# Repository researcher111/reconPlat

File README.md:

reconPlat
=========

Reconfigurable platform for prototyping wearables

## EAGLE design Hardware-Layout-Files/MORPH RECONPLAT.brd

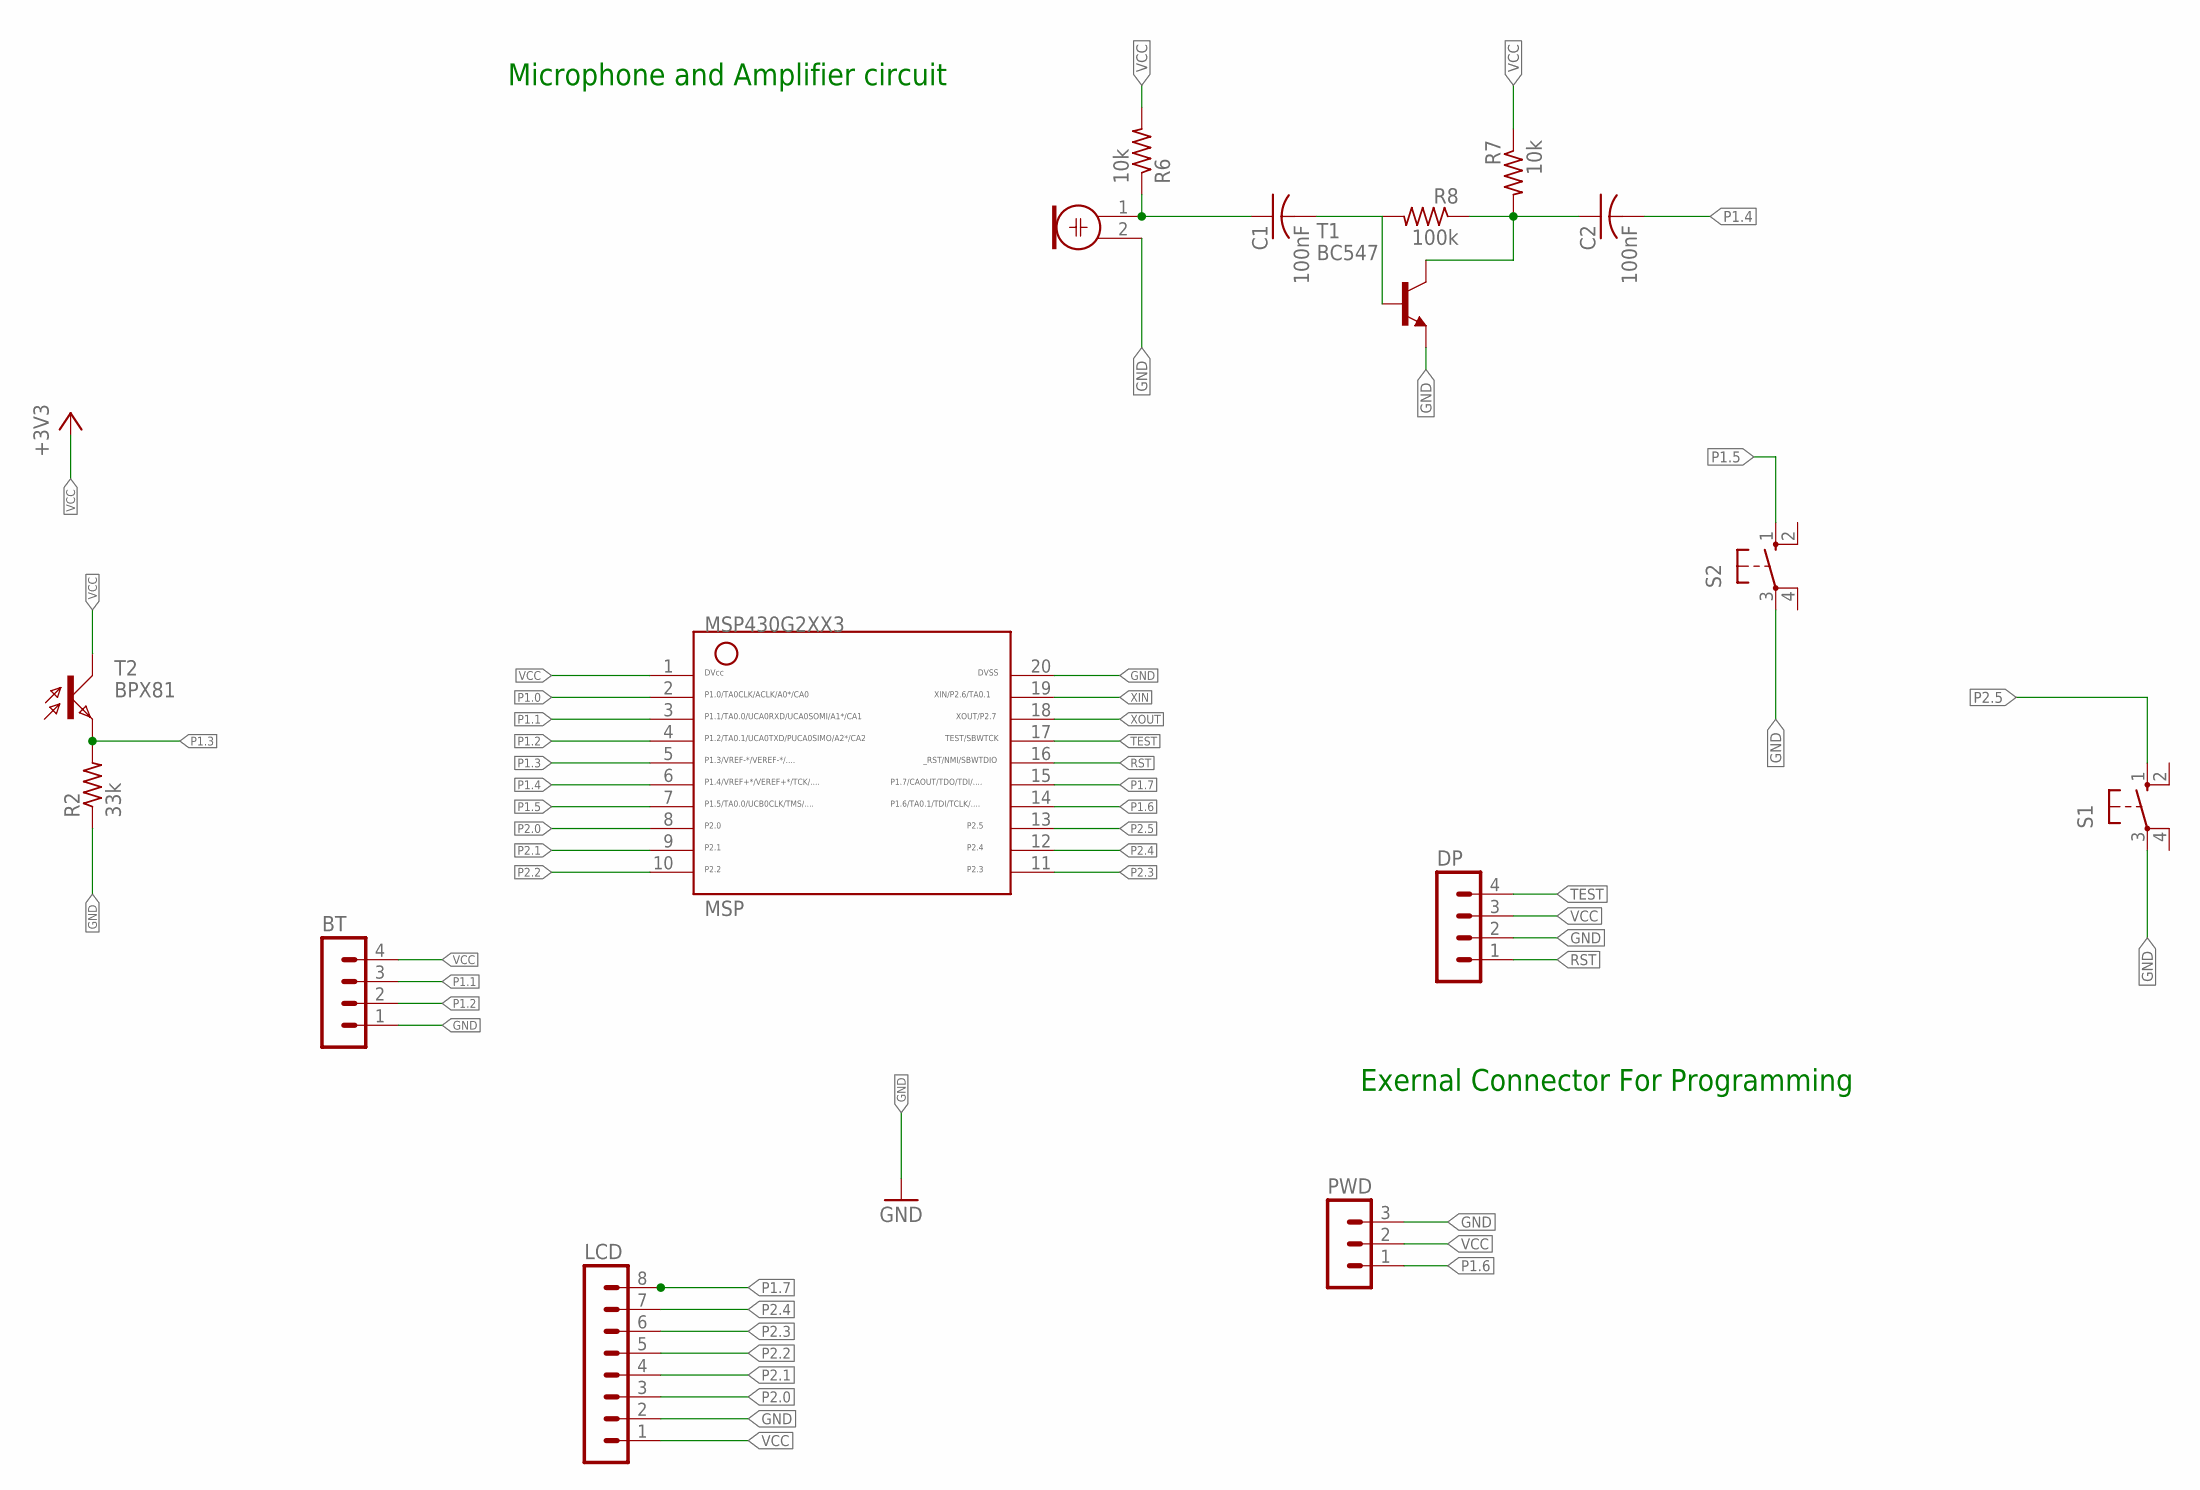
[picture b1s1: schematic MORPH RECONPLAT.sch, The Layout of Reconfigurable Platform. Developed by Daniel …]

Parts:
BT: MA04-1
C1, C2: 100nF; C025-025X050
DP: MA04-1
LCD: MA08-1
M1: ELECTRET_MICROPHON-WM-64PC/64PK; WM-64PC/64PK
MSP: G2XX3---N20; N20
PWD: MA03-1
R2: 33k; 0207/10
R6, R7: 10k; 0207/10
R8: 100k; 0207/10
S1, S2: 10-XX; B3F-10XX
T1: BC547; TO92
T2: BPX81

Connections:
GND: BT.1, DP.2, LCD.2, M1.2, MSP.20, PWD.3, R2.1, S1.3, S2.3, T1.1 (E)
unnamed: C1.1, M1.1, R6.1
unnamed: C1.2, R8.2, T1.2 (B)
unnamed: C2.1, R7.2, R8.1, T1.3 (C)
P1.0: MSP.2
P1.1: BT.3, MSP.3
P1.2: BT.2, MSP.4
P1.3: MSP.5, R2.2, T2.E
P1.4: C2.2, MSP.6
P1.5: MSP.7, S2.1 (S)
P1.6: MSP.14, PWD.1
P1.7: LCD.8, MSP.15
P2.0: LCD.3, MSP.8
P2.1: LCD.4, MSP.9
P2.2: LCD.5, MSP.10
P2.3: LCD.6, MSP.11
P2.4: LCD.7, MSP.12
P2.5: MSP.13, S1.1 (S)
RST: DP.1, MSP.16
TEST: DP.4, MSP.17
VCC: BT.4, DP.3, LCD.1, MSP.1, PWD.2, R6.2, R7.1, T2.C
XIN: MSP.19
XOUT: MSP.18

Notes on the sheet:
Microphone and Amplifier circuit
Exernal Connector For Programming

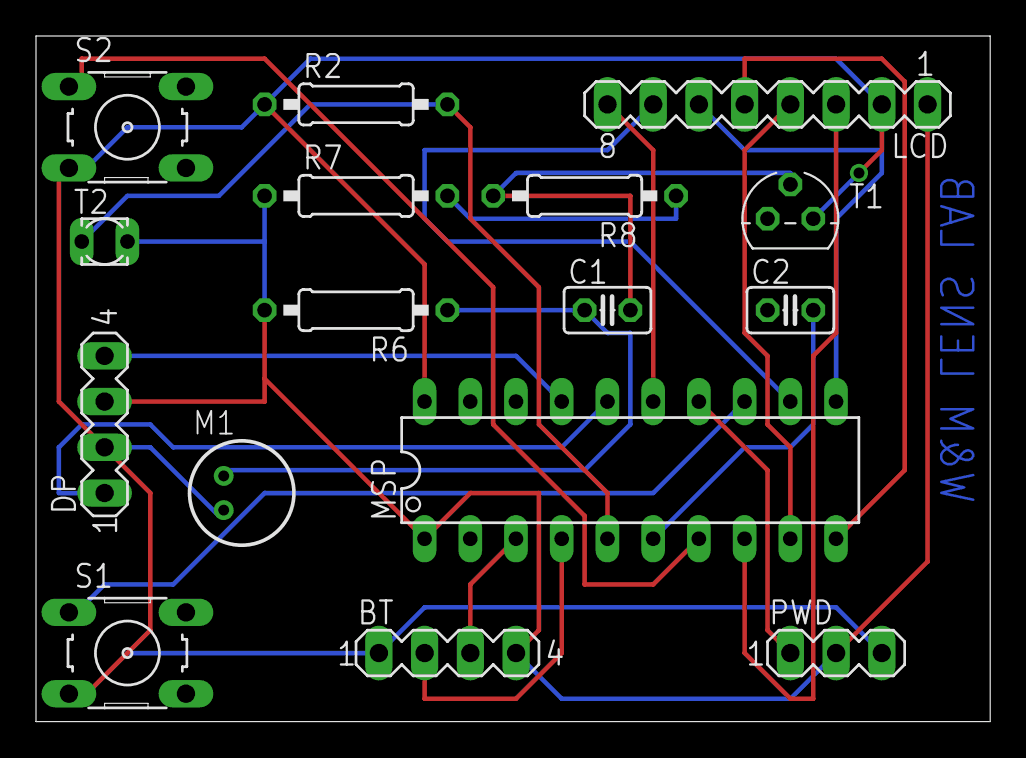
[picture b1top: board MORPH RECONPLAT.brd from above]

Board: 2 copper layers, 53.0 x 38.1 mm, 16 parts (0 on the bottom side), 20 nets.

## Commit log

2014-07-09 Create gh-pages branch via GitHub
2014-07-12 Hardware files for board
2014-07-12 Software stuff
2014-07-12 Hardware software folders
2014-07-12 Hardware files
2014-07-12 Remove Hardware folder
2014-10-28 Layout Upldate
2014-10-28 Updated software
2014-10-28 final changes
2014-10-28 mic library update
2014-10-29 module sense library update"
